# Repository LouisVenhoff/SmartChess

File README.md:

# SmartChessBoard

Repository for development of an Smart Chess Board (Hardware and Software)

Further coming soon...

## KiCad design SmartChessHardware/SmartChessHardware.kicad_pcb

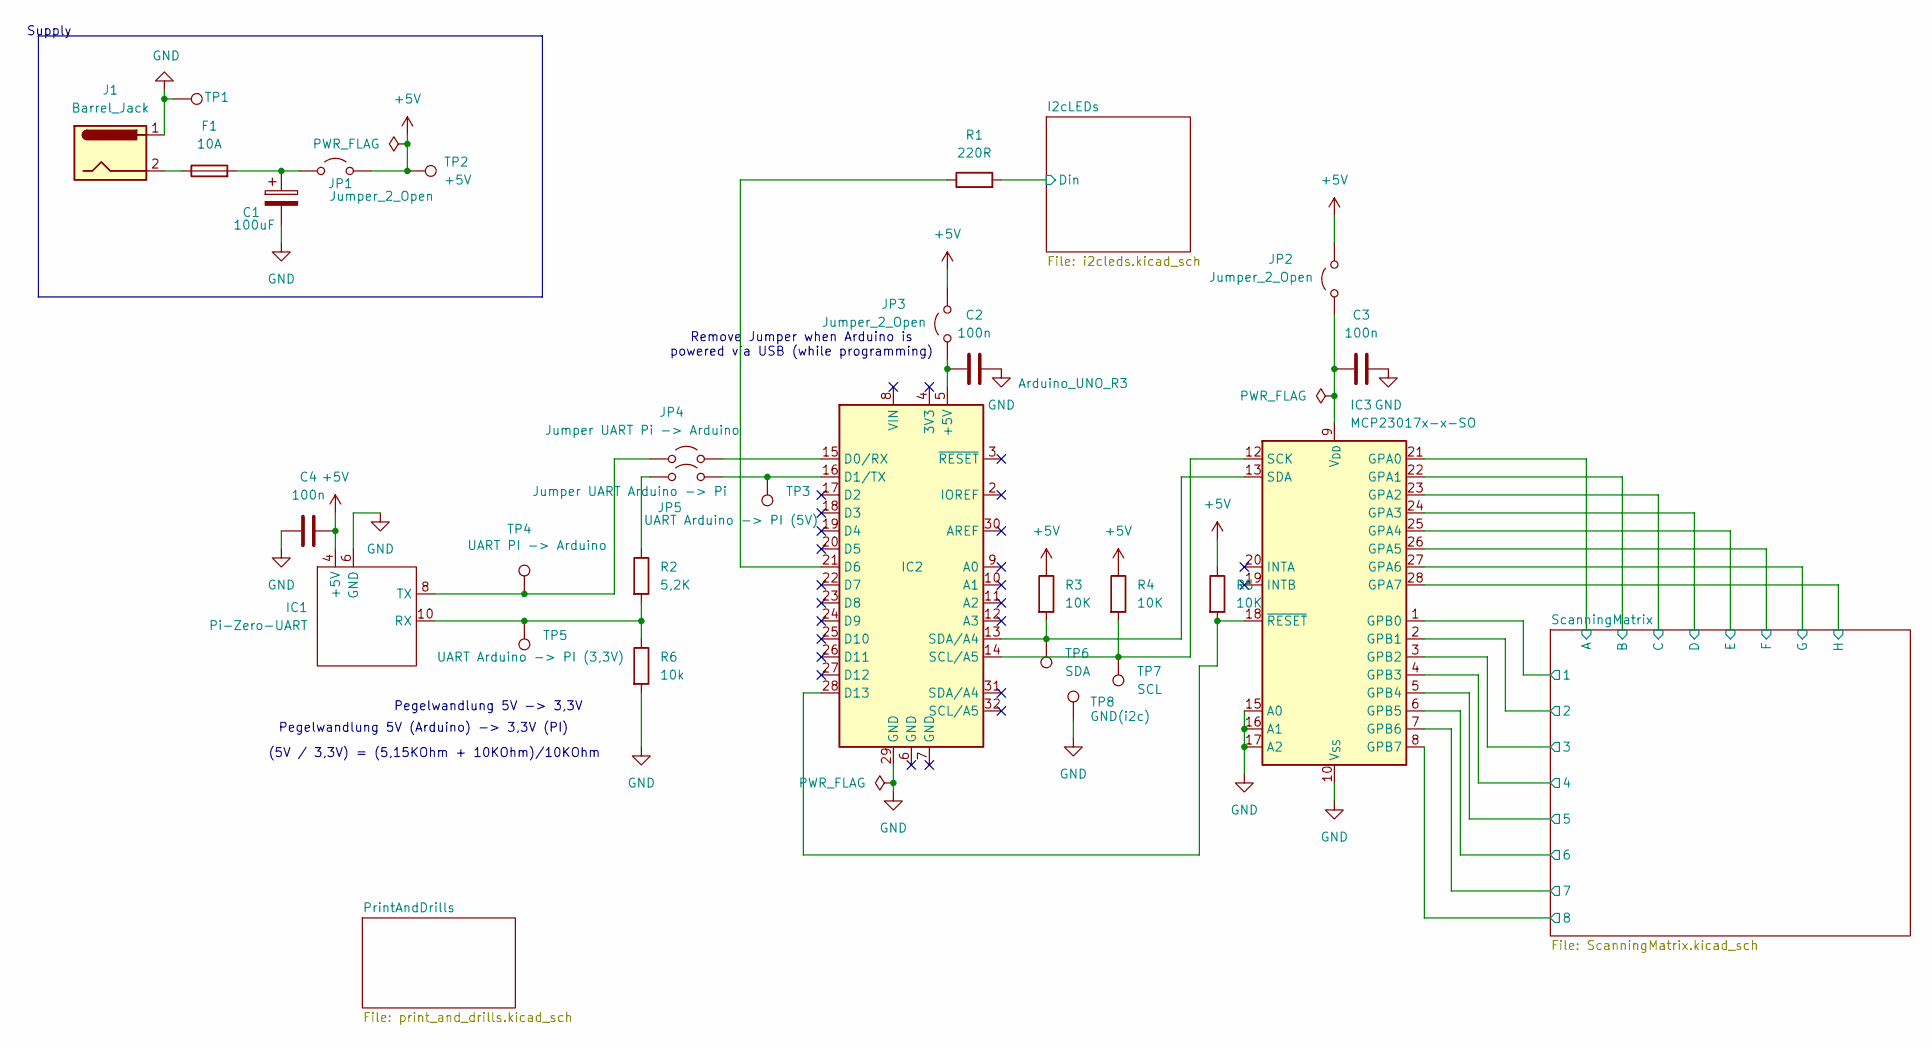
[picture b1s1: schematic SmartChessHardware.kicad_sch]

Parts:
C1: 100uF; CP_Radial_D6.3mm_P2.50mm
C2, C3, C4: 100n; C_0603_1608Metric
F1: 10A; Fuse_0603_1608Metric
IC1: Pi-Zero-UART; Raspberry_Pi_Zero_Socketed_THT_FaceDown_MountingHoles
IC2: Arduino_UNO_R3
IC3: MCP23017x-x-SO; SOIC-28W_7.5x17.9mm_P1.27mm
J1: Barrel_Jack; BarrelJack_GCT_DCJ200-10-A_Horizontal
JP1, JP2, JP3: Jumper_2_Open; PinHeader_1x02_P1.00mm_Vertical
JP4: Jumper UART Pi -> Arduino; PinHeader_1x02_P1.00mm_Vertical
JP5: Jumper UART Arduino -> Pi; PinHeader_1x02_P1.00mm_Vertical
R1: 220R; R_0603_1608Metric
R2: 5,2K; R_0603_1608Metric
R3, R4, R5: 10K; R_0603_1608Metric
R6: 10k; R_0603_1608Metric
TP1: GND; TestPoint_THTPad_D2.0mm_Drill1.0mm
TP2: +5V; TestPoint_THTPad_D2.0mm_Drill1.0mm
TP3: UART Arduino -> PI (5V); TestPoint_THTPad_D2.0mm_Drill1.0mm
TP4: UART PI -> Arduino; TestPoint_THTPad_D2.0mm_Drill1.0mm
TP5: UART Arduino -> PI (3,3V); TestPoint_THTPad_D2.0mm_Drill1.0mm
TP6: SDA; TestPoint_THTPad_D2.0mm_Drill1.0mm
TP7: SCL; TestPoint_THTPad_D2.0mm_Drill1.0mm
TP8: GND(i2c); TestPoint_THTPad_D2.0mm_Drill1.0mm

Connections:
+5V: C4.1, IC1.4 (+5V), JP1.2 (B), JP2.2 (B), JP3.2 (B), R3.1, R4.1, R5.1, TP2.1 (1_1); also elsewhere on the board
/I2cLEDs/Din: R1.2; also elsewhere on the board
/ScanningMatrix/1: IC3.1 (GPB0); also elsewhere on the board
/ScanningMatrix/2: IC3.2 (GPB1); also elsewhere on the board
/ScanningMatrix/3: IC3.3 (GPB2); also elsewhere on the board
/ScanningMatrix/4: IC3.4 (GPB3); also elsewhere on the board
/ScanningMatrix/5: IC3.5 (GPB4); also elsewhere on the board
/ScanningMatrix/6: IC3.6 (GPB5); also elsewhere on the board
/ScanningMatrix/7: IC3.7 (GPB6); also elsewhere on the board
/ScanningMatrix/8: IC3.8 (GPB7); also elsewhere on the board
/ScanningMatrix/A: IC3.21 (GPA0); also elsewhere on the board
/ScanningMatrix/B: IC3.22 (GPA1); also elsewhere on the board
/ScanningMatrix/C: IC3.23 (GPA2); also elsewhere on the board
/ScanningMatrix/D: IC3.24 (GPA3); also elsewhere on the board
/ScanningMatrix/E: IC3.25 (GPA4); also elsewhere on the board
/ScanningMatrix/F: IC3.26 (GPA5); also elsewhere on the board
/ScanningMatrix/G: IC3.27 (GPA6); also elsewhere on the board
/ScanningMatrix/H: IC3.28 (GPA7); also elsewhere on the board
GND: C1.2, C2.2, C3.2, C4.2, IC1.6 (GND), IC2.29 (GND), IC3.10 (V_{SS}), IC3.15 (A0), IC3.16 (A1), IC3.17 (A2), J1.1, R6.2, TP1.1 (1_1), TP8.1 (1_1); also elsewhere on the board
unnamed: F1.1, J1.2
unnamed: IC1.10 (RX), R2.2, R6.1, TP5.1 (1_1)
unnamed: IC1.8 (TX), JP4.1 (A), TP4.1 (1_1)
unnamed: C2.1, IC2.5 (+5V), JP3.1 (A)
unnamed: IC2.15 (D0/RX), JP4.2 (B)
unnamed: IC2.16 (D1/TX), JP5.2 (B), TP3.1 (1_1)
unnamed: IC2.21 (D6), R1.1
unnamed: IC2.28 (D13), IC3.18 (~RESET), R5.2
unnamed: IC2.14 (SCL/A5), IC3.12 (SCK), R4.2, TP7.1 (1_1)
unnamed: IC2.13 (SDA/A4), IC3.13 (SDA), R3.2, TP6.1 (1_1)
unnamed: C3.1, IC3.9 (V_{DD}), JP2.1 (A)
unnamed: C1.1, F1.2, JP1.1 (A)
unnamed: JP5.1 (A), R2.1

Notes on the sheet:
(5V / 3,3V) = (5,15KOhm + 10KOhm)/10KOhm
Remove Jumper when Arduino is powered via USB (while programming)
Pegelwandlung 5V -> 3,3V
Pegelwandlung 5V (Arduino) -> 3,3V (PI)
Supply

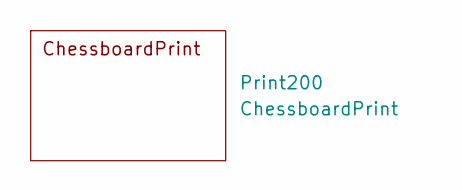
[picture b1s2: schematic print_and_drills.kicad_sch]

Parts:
Print200: ChessboardPrint; ChessBoard

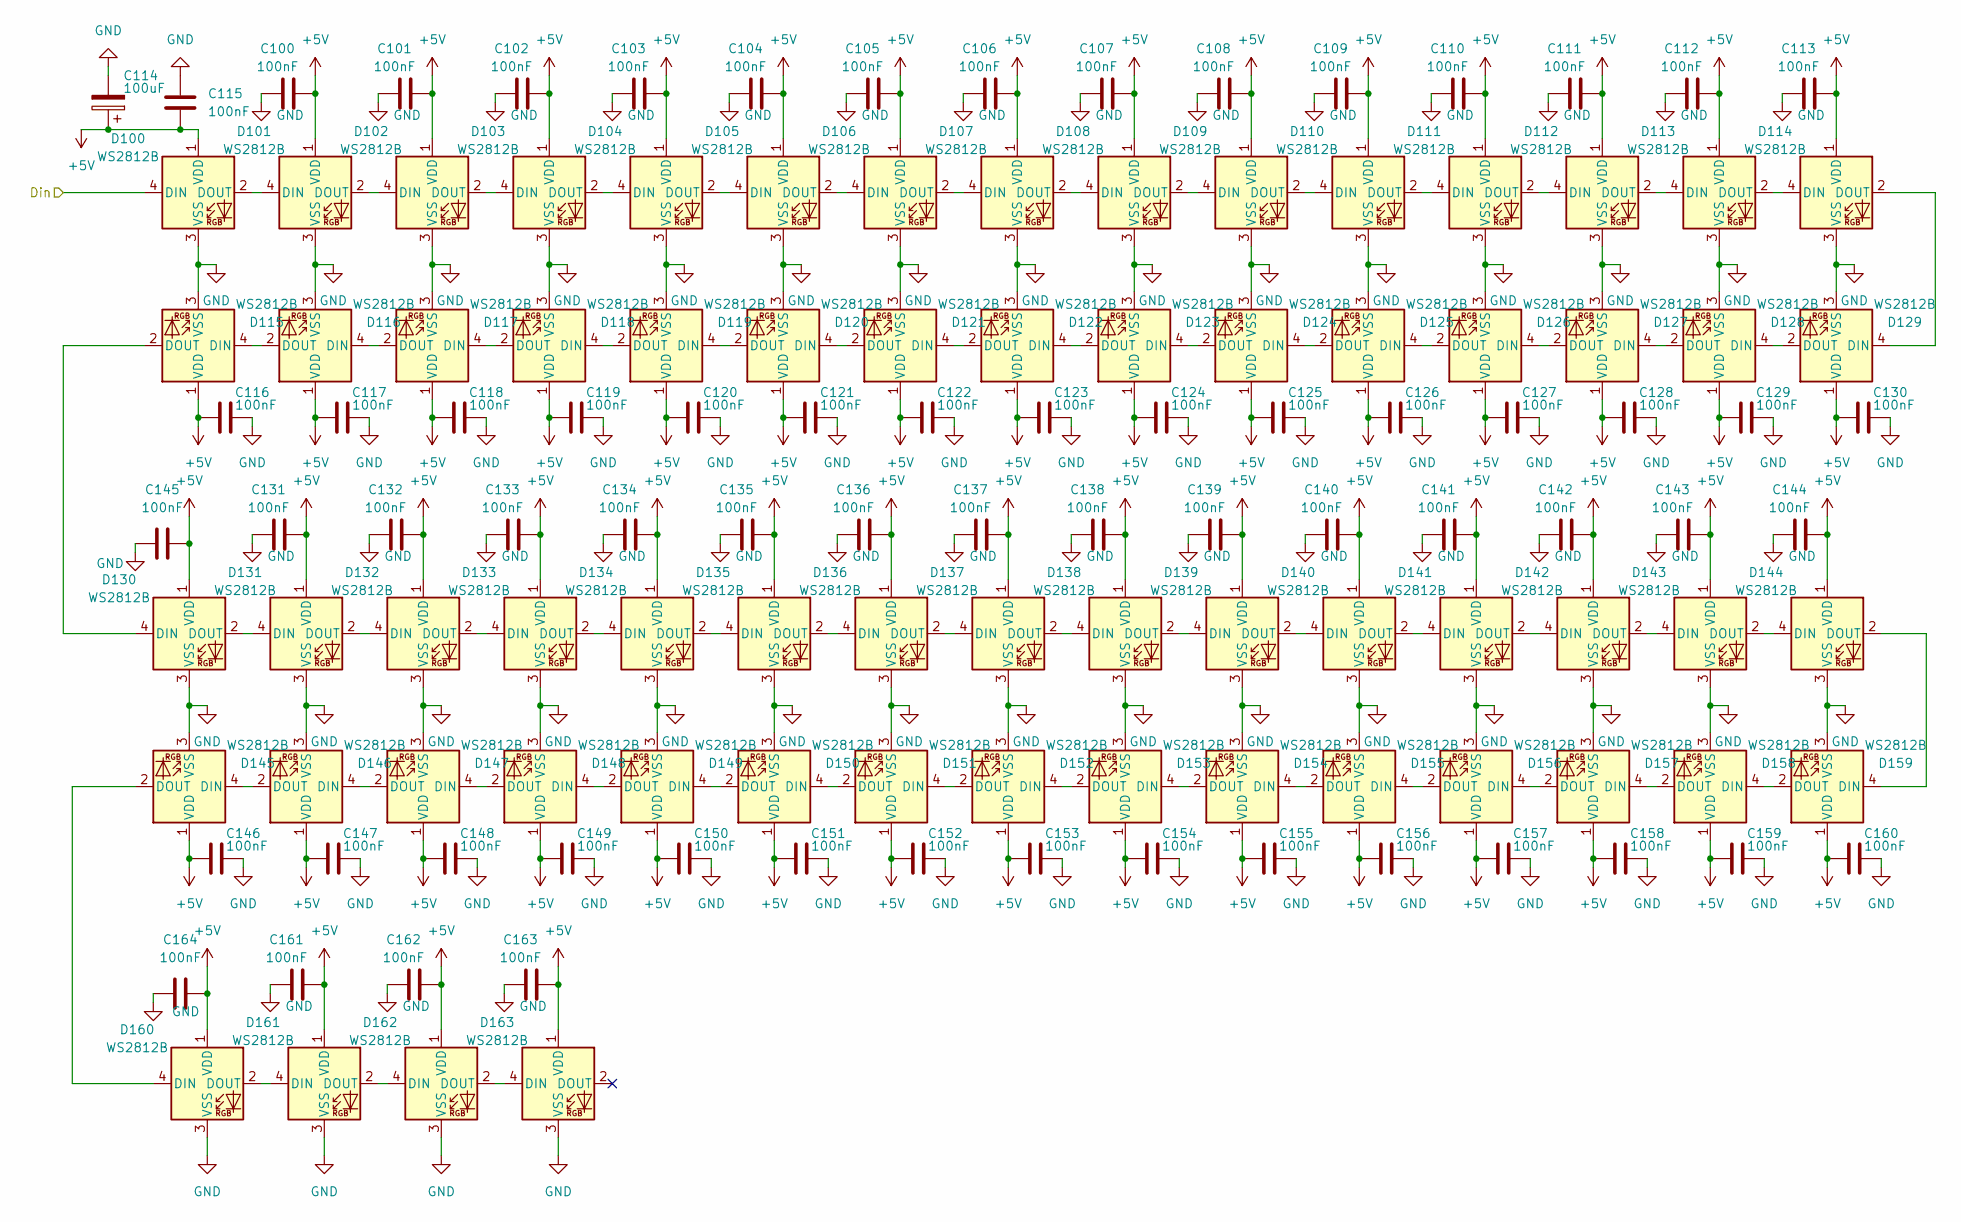
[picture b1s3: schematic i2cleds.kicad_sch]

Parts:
C100, C101, C102, C103, C104, C105, C106, C107, C108, C109, C110, C111, C112, C113, C115, C116, C117, C118, C119, C120, C121, C122, C123, C124, C125, C126, C127, C128, C129, C130, C131, C132, C133, C134, C135, C136, C137, C138, C139, C140, C141, C142, C143, C144, C145, C146, C147, C148, C149, C150, C151, C152, C153, C154, C155, C156, C157, C158, C159, C160, C161, C162, C163, C164: 100nF; C_0603_1608Metric
C114: 100uF; CP_Radial_D6.3mm_P2.50mm
D100, D101, D102, D103, D104, D105, D106, D107, D108, D109, D110, D111, D112, D113, D114, D115, D116, D117, D118, D119, D120, D121, D122, D123, D124, D125, D126, D127, D128, D129, D130, D131, D132, D133, D134, D135, D136, D137, D138, D139, D140, D141, D142, D143, D144, D145, D146, D147, D148, D149, D150, D151, D152, D153, D154, D155, D156, D157, D158, D159, D160, D161, D162, D163: WS2812B; LED_WS2812B_PLCC4_5.0x5.0mm_P3.2mm

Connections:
+5V: C100.2, C101.2, C102.2, C103.2, C104.2, C105.2, C106.2, C107.2, C108.2, C109.2, C110.2, C111.2, C112.2, C113.2, C114.1, C115.2, C116.1, C117.1, C118.1, C119.1, C120.1, C121.1, C122.1, C123.1, C124.1, C125.1, C126.1, C127.1, C128.1, C129.1, C130.1, C131.2, C132.2, C133.2, C134.2, C135.2, C136.2, C137.2, C138.2, C139.2, C140.2, C141.2, C142.2, C143.2, C144.2, C145.2, C146.1, C147.1, C148.1, C149.1, C150.1, C151.1, C152.1, C153.1, C154.1, C155.1, C156.1, C157.1, C158.1, C159.1, C160.1, C161.2, C162.2, C163.2, C164.2, D100.1 (VDD), D101.1 (VDD), D102.1 (VDD), D103.1 (VDD), D104.1 (VDD), D105.1 (VDD), D106.1 (VDD), D107.1 (VDD), D108.1 (VDD), D109.1 (VDD), D110.1 (VDD), D111.1 (VDD), D112.1 (VDD), D113.1 (VDD), D114.1 (VDD), D115.1 (VDD), D116.1 (VDD), D117.1 (VDD), D118.1 (VDD), D119.1 (VDD), D120.1 (VDD), D121.1 (VDD), D122.1 (VDD), D123.1 (VDD), D124.1 (VDD), D125.1 (VDD), D126.1 (VDD), D127.1 (VDD), D128.1 (VDD), D129.1 (VDD), D130.1 (VDD), D131.1 (VDD), D132.1 (VDD), D133.1 (VDD), D134.1 (VDD), D135.1 (VDD), D136.1 (VDD), D137.1 (VDD), D138.1 (VDD), D139.1 (VDD), D140.1 (VDD), D141.1 (VDD), D142.1 (VDD), D143.1 (VDD), D144.1 (VDD), D145.1 (VDD), D146.1 (VDD), D147.1 (VDD), D148.1 (VDD), D149.1 (VDD), D150.1 (VDD), D151.1 (VDD), D152.1 (VDD), D153.1 (VDD), D154.1 (VDD), D155.1 (VDD), D156.1 (VDD), D157.1 (VDD), D158.1 (VDD), D159.1 (VDD), D160.1 (VDD), D161.1 (VDD), D162.1 (VDD), D163.1 (VDD); also elsewhere on the board
/I2cLEDs/Din: D100.4 (DIN); also elsewhere on the board
GND: C100.1, C101.1, C102.1, C103.1, C104.1, C105.1, C106.1, C107.1, C108.1, C109.1, C110.1, C111.1, C112.1, C113.1, C114.2, C115.1, C116.2, C117.2, C118.2, C119.2, C120.2, C121.2, C122.2, C123.2, C124.2, C125.2, C126.2, C127.2, C128.2, C129.2, C130.2, C131.1, C132.1, C133.1, C134.1, C135.1, C136.1, C137.1, C138.1, C139.1, C140.1, C141.1, C142.1, C143.1, C144.1, C145.1, C146.2, C147.2, C148.2, C149.2, C150.2, C151.2, C152.2, C153.2, C154.2, C155.2, C156.2, C157.2, C158.2, C159.2, C160.2, C161.1, C162.1, C163.1, C164.1, D100.3 (VSS), D101.3 (VSS), D102.3 (VSS), D103.3 (VSS), D104.3 (VSS), D105.3 (VSS), D106.3 (VSS), D107.3 (VSS), D108.3 (VSS), D109.3 (VSS), D110.3 (VSS), D111.3 (VSS), D112.3 (VSS), D113.3 (VSS), D114.3 (VSS), D115.3 (VSS), D116.3 (VSS), D117.3 (VSS), D118.3 (VSS), D119.3 (VSS), D120.3 (VSS), D121.3 (VSS), D122.3 (VSS), D123.3 (VSS), D124.3 (VSS), D125.3 (VSS), D126.3 (VSS), D127.3 (VSS), D128.3 (VSS), D129.3 (VSS), D130.3 (VSS), D131.3 (VSS), D132.3 (VSS), D133.3 (VSS), D134.3 (VSS), D135.3 (VSS), D136.3 (VSS), D137.3 (VSS), D138.3 (VSS), D139.3 (VSS), D140.3 (VSS), D141.3 (VSS), D142.3 (VSS), D143.3 (VSS), D144.3 (VSS), D145.3 (VSS), D146.3 (VSS), D147.3 (VSS), D148.3 (VSS), D149.3 (VSS), D150.3 (VSS), D151.3 (VSS), D152.3 (VSS), D153.3 (VSS), D154.3 (VSS), D155.3 (VSS), D156.3 (VSS), D157.3 (VSS), D158.3 (VSS), D159.3 (VSS), D160.3 (VSS), D161.3 (VSS), D162.3 (VSS), D163.3 (VSS); also elsewhere on the board
unnamed: D100.2 (DOUT), D101.4 (DIN)
unnamed: D101.2 (DOUT), D102.4 (DIN)
unnamed: D102.2 (DOUT), D103.4 (DIN)
unnamed: D103.2 (DOUT), D104.4 (DIN)
unnamed: D104.2 (DOUT), D105.4 (DIN)
unnamed: D105.2 (DOUT), D106.4 (DIN)
unnamed: D106.2 (DOUT), D107.4 (DIN)
unnamed: D107.2 (DOUT), D108.4 (DIN)
unnamed: D108.2 (DOUT), D109.4 (DIN)
unnamed: D109.2 (DOUT), D110.4 (DIN)
unnamed: D110.2 (DOUT), D111.4 (DIN)
unnamed: D111.2 (DOUT), D112.4 (DIN)
unnamed: D112.2 (DOUT), D113.4 (DIN)
unnamed: D113.2 (DOUT), D114.4 (DIN)
unnamed: D114.2 (DOUT), D129.4 (DIN)
unnamed: D115.4 (DIN), D116.2 (DOUT)
unnamed: D115.2 (DOUT), D130.4 (DIN)
unnamed: D116.4 (DIN), D117.2 (DOUT)
unnamed: D117.4 (DIN), D118.2 (DOUT)
unnamed: D118.4 (DIN), D119.2 (DOUT)
unnamed: D119.4 (DIN), D120.2 (DOUT)
unnamed: D120.4 (DIN), D121.2 (DOUT)
unnamed: D121.4 (DIN), D122.2 (DOUT)
unnamed: D122.4 (DIN), D123.2 (DOUT)
unnamed: D123.4 (DIN), D124.2 (DOUT)
unnamed: D124.4 (DIN), D125.2 (DOUT)
unnamed: D125.4 (DIN), D126.2 (DOUT)
unnamed: D126.4 (DIN), D127.2 (DOUT)
unnamed: D127.4 (DIN), D128.2 (DOUT)
unnamed: D128.4 (DIN), D129.2 (DOUT)
unnamed: D130.2 (DOUT), D131.4 (DIN)
unnamed: D131.2 (DOUT), D132.4 (DIN)
unnamed: D132.2 (DOUT), D133.4 (DIN)
unnamed: D133.2 (DOUT), D134.4 (DIN)
unnamed: D134.2 (DOUT), D135.4 (DIN)
unnamed: D135.2 (DOUT), D136.4 (DIN)
unnamed: D136.2 (DOUT), D137.4 (DIN)
unnamed: D137.2 (DOUT), D138.4 (DIN)
unnamed: D138.2 (DOUT), D139.4 (DIN)
unnamed: D139.2 (DOUT), D140.4 (DIN)
unnamed: D140.2 (DOUT), D141.4 (DIN)
unnamed: D141.2 (DOUT), D142.4 (DIN)
unnamed: D142.2 (DOUT), D143.4 (DIN)
unnamed: D143.2 (DOUT), D144.4 (DIN)
unnamed: D144.2 (DOUT), D159.4 (DIN)
unnamed: D145.4 (DIN), D146.2 (DOUT)
unnamed: D145.2 (DOUT), D160.4 (DIN)
unnamed: D146.4 (DIN), D147.2 (DOUT)
unnamed: D147.4 (DIN), D148.2 (DOUT)
unnamed: D148.4 (DIN), D149.2 (DOUT)
unnamed: D149.4 (DIN), D150.2 (DOUT)
unnamed: D150.4 (DIN), D151.2 (DOUT)
unnamed: D151.4 (DIN), D152.2 (DOUT)
unnamed: D152.4 (DIN), D153.2 (DOUT)
unnamed: D153.4 (DIN), D154.2 (DOUT)
unnamed: D154.4 (DIN), D155.2 (DOUT)
unnamed: D155.4 (DIN), D156.2 (DOUT)
unnamed: D156.4 (DIN), D157.2 (DOUT)
unnamed: D157.4 (DIN), D158.2 (DOUT)
unnamed: D158.4 (DIN), D159.2 (DOUT)
unnamed: D160.2 (DOUT), D161.4 (DIN)
unnamed: D161.2 (DOUT), D162.4 (DIN)
unnamed: D162.2 (DOUT), D163.4 (DIN)

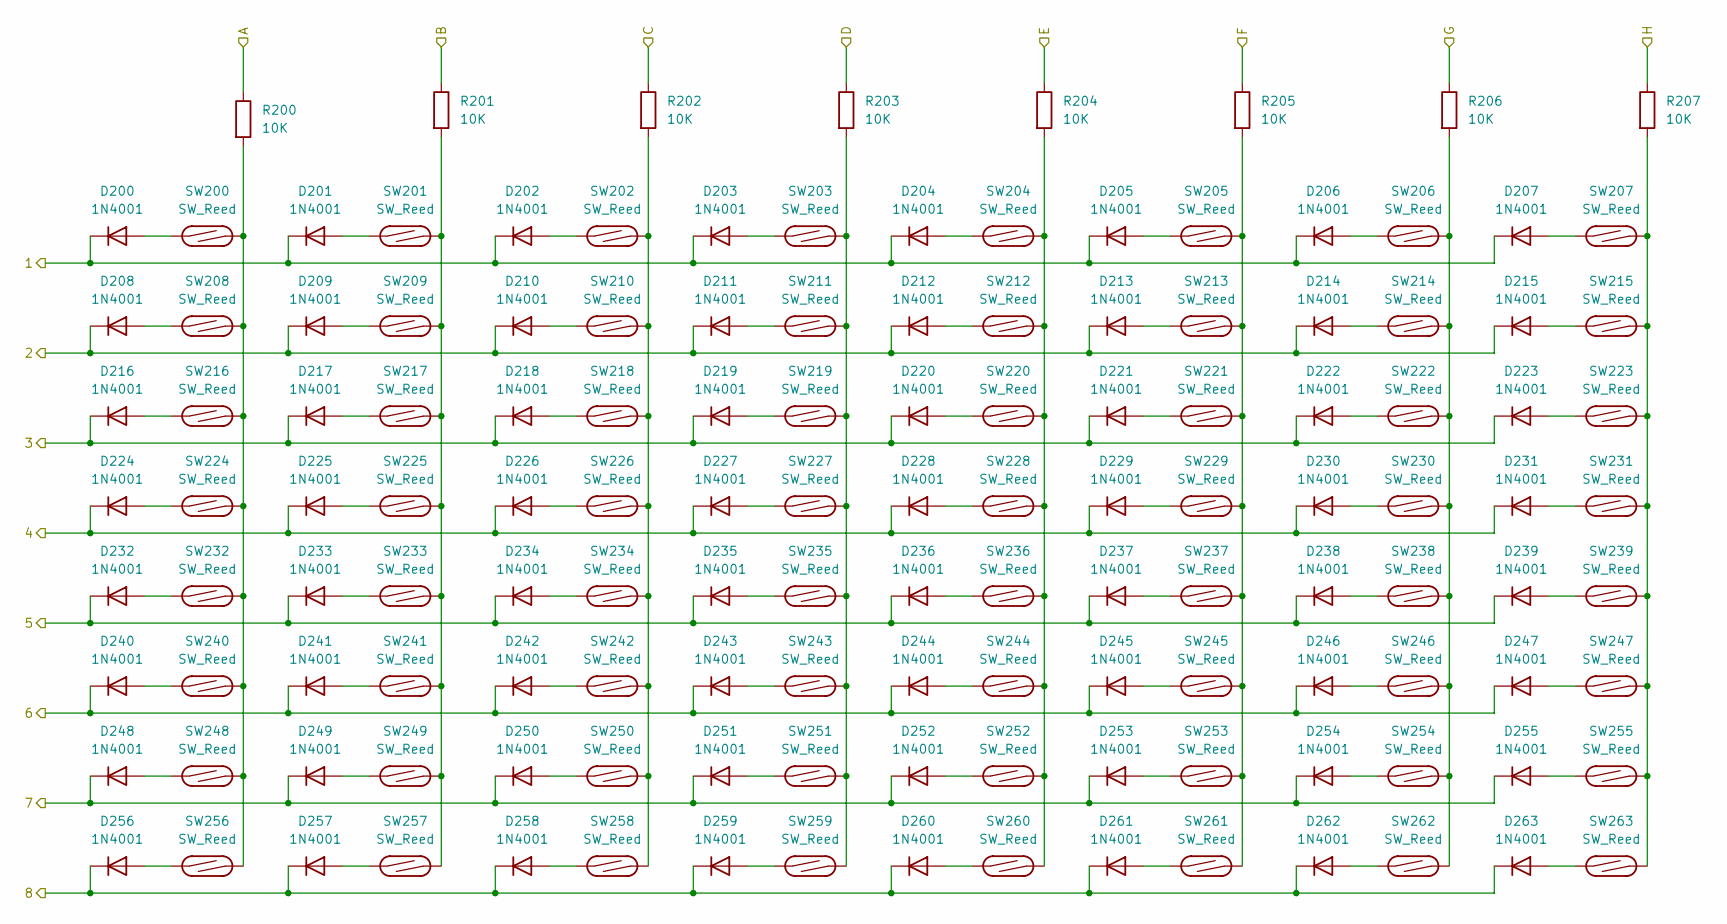
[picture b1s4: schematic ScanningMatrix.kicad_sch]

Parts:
D200, D201, D202, D203, D204, D205, D206, D207, D208, D209, D210, D211, D212, D213, D214, D215, D216, D217, D218, D219, D220, D221, D222, D223, D224, D225, D226, D227, D228, D229, D230, D231, D232, D233, D234, D235, D236, D237, D238, D239, D240, D241, D242, D243, D244, D245, D246, D247, D248, D249, D250, D251, D252, D253, D254, D255, D256, D257, D258, D259, D260, D261, D262, D263: 1N4001; D_SMA
R200, R201, R202, R203, R204, R205, R206, R207: 10K; R_0603_1608Metric
SW200, SW201, SW202, SW203, SW204, SW205, SW206, SW207, SW208, SW209, SW210, SW211, SW212, SW213, SW214, SW215, SW216, SW217, SW218, SW219, SW220, SW221, SW222, SW223, SW224, SW225, SW226, SW227, SW228, SW229, SW230, SW231, SW232, SW233, SW234, SW235, SW236, SW237, SW238, SW239, SW240, SW241, SW242, SW243, SW244, SW245, SW246, SW247, SW248, SW249, SW250, SW251, SW252, SW253, SW254, SW255, SW256, SW257, SW258, SW259, SW260, SW261, SW262, SW263: SW_Reed; R_Axial_DIN0309_L9.0mm_D3.2mm_P20.32mm_Horizontal

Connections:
/ScanningMatrix/1: D200.1 (K), D201.1 (K), D202.1 (K), D203.1 (K), D204.1 (K), D205.1 (K), D206.1 (K), D207.1 (K); also elsewhere on the board
/ScanningMatrix/2: D208.1 (K), D209.1 (K), D210.1 (K), D211.1 (K), D212.1 (K), D213.1 (K), D214.1 (K), D215.1 (K); also elsewhere on the board
/ScanningMatrix/3: D216.1 (K), D217.1 (K), D218.1 (K), D219.1 (K), D220.1 (K), D221.1 (K), D222.1 (K), D223.1 (K); also elsewhere on the board
/ScanningMatrix/4: D224.1 (K), D225.1 (K), D226.1 (K), D227.1 (K), D228.1 (K), D229.1 (K), D230.1 (K), D231.1 (K); also elsewhere on the board
/ScanningMatrix/5: D232.1 (K), D233.1 (K), D234.1 (K), D235.1 (K), D236.1 (K), D237.1 (K), D238.1 (K), D239.1 (K); also elsewhere on the board
/ScanningMatrix/6: D240.1 (K), D241.1 (K), D242.1 (K), D243.1 (K), D244.1 (K), D245.1 (K), D246.1 (K), D247.1 (K); also elsewhere on the board
/ScanningMatrix/7: D248.1 (K), D249.1 (K), D250.1 (K), D251.1 (K), D252.1 (K), D253.1 (K), D254.1 (K), D255.1 (K); also elsewhere on the board
/ScanningMatrix/8: D256.1 (K), D257.1 (K), D258.1 (K), D259.1 (K), D260.1 (K), D261.1 (K), D262.1 (K), D263.1 (K); also elsewhere on the board
/ScanningMatrix/A: R200.1; also elsewhere on the board
/ScanningMatrix/B: R201.1; also elsewhere on the board
/ScanningMatrix/C: R202.1; also elsewhere on the board
/ScanningMatrix/D: R203.1; also elsewhere on the board
/ScanningMatrix/E: R204.1; also elsewhere on the board
/ScanningMatrix/F: R205.1; also elsewhere on the board
/ScanningMatrix/G: R206.1; also elsewhere on the board
/ScanningMatrix/H: R207.1; also elsewhere on the board
unnamed: D200.2 (A), SW200.1
unnamed: D201.2 (A), SW201.1
unnamed: D202.2 (A), SW202.1
unnamed: D203.2 (A), SW203.1
unnamed: D204.2 (A), SW204.1
unnamed: D205.2 (A), SW205.1
unnamed: D206.2 (A), SW206.1
unnamed: D207.2 (A), SW207.1
unnamed: D208.2 (A), SW208.1
unnamed: D209.2 (A), SW209.1
unnamed: D210.2 (A), SW210.1
unnamed: D211.2 (A), SW211.1
unnamed: D212.2 (A), SW212.1
unnamed: D213.2 (A), SW213.1
unnamed: D214.2 (A), SW214.1
unnamed: D215.2 (A), SW215.1
unnamed: D216.2 (A), SW216.1
unnamed: D217.2 (A), SW217.1
unnamed: D218.2 (A), SW218.1
unnamed: D219.2 (A), SW219.1
unnamed: D220.2 (A), SW220.1
unnamed: D221.2 (A), SW221.1
unnamed: D222.2 (A), SW222.1
unnamed: D223.2 (A), SW223.1
unnamed: D224.2 (A), SW224.1
unnamed: D225.2 (A), SW225.1
unnamed: D226.2 (A), SW226.1
unnamed: D227.2 (A), SW227.1
unnamed: D228.2 (A), SW228.1
unnamed: D229.2 (A), SW229.1
unnamed: D230.2 (A), SW230.1
unnamed: D231.2 (A), SW231.1
unnamed: D232.2 (A), SW232.1
unnamed: D233.2 (A), SW233.1
unnamed: D234.2 (A), SW234.1
unnamed: D235.2 (A), SW235.1
unnamed: D236.2 (A), SW236.1
unnamed: D237.2 (A), SW237.1
unnamed: D238.2 (A), SW238.1
unnamed: D239.2 (A), SW239.1
unnamed: D240.2 (A), SW240.1
unnamed: D241.2 (A), SW241.1
unnamed: D242.2 (A), SW242.1
unnamed: D243.2 (A), SW243.1
unnamed: D244.2 (A), SW244.1
unnamed: D245.2 (A), SW245.1
unnamed: D246.2 (A), SW246.1
unnamed: D247.2 (A), SW247.1
unnamed: D248.2 (A), SW248.1
unnamed: D249.2 (A), SW249.1
unnamed: D250.2 (A), SW250.1
unnamed: D251.2 (A), SW251.1
unnamed: D252.2 (A), SW252.1
unnamed: D253.2 (A), SW253.1
unnamed: D254.2 (A), SW254.1
unnamed: D255.2 (A), SW255.1
unnamed: D256.2 (A), SW256.1
unnamed: D257.2 (A), SW257.1
unnamed: D258.2 (A), SW258.1
unnamed: D259.2 (A), SW259.1
unnamed: D260.2 (A), SW260.1
unnamed: D261.2 (A), SW261.1
unnamed: D262.2 (A), SW262.1
unnamed: D263.2 (A), SW263.1
unnamed: R200.2, SW200.2, SW208.2, SW216.2, SW224.2, SW232.2, SW240.2, SW248.2, SW256.2
unnamed: R201.2, SW201.2, SW209.2, SW217.2, SW225.2, SW233.2, SW241.2, SW249.2, SW257.2
unnamed: R202.2, SW202.2, SW210.2, SW218.2, SW226.2, SW234.2, SW242.2, SW250.2, SW258.2
unnamed: R203.2, SW203.2, SW211.2, SW219.2, SW227.2, SW235.2, SW243.2, SW251.2, SW259.2
unnamed: R204.2, SW204.2, SW212.2, SW220.2, SW228.2, SW236.2, SW244.2, SW252.2, SW260.2
unnamed: R205.2, SW205.2, SW213.2, SW221.2, SW229.2, SW237.2, SW245.2, SW253.2, SW261.2
unnamed: R206.2, SW206.2, SW214.2, SW222.2, SW230.2, SW238.2, SW246.2, SW254.2, SW262.2
unnamed: R207.2, SW207.2, SW215.2, SW223.2, SW231.2, SW239.2, SW247.2, SW255.2, SW263.2

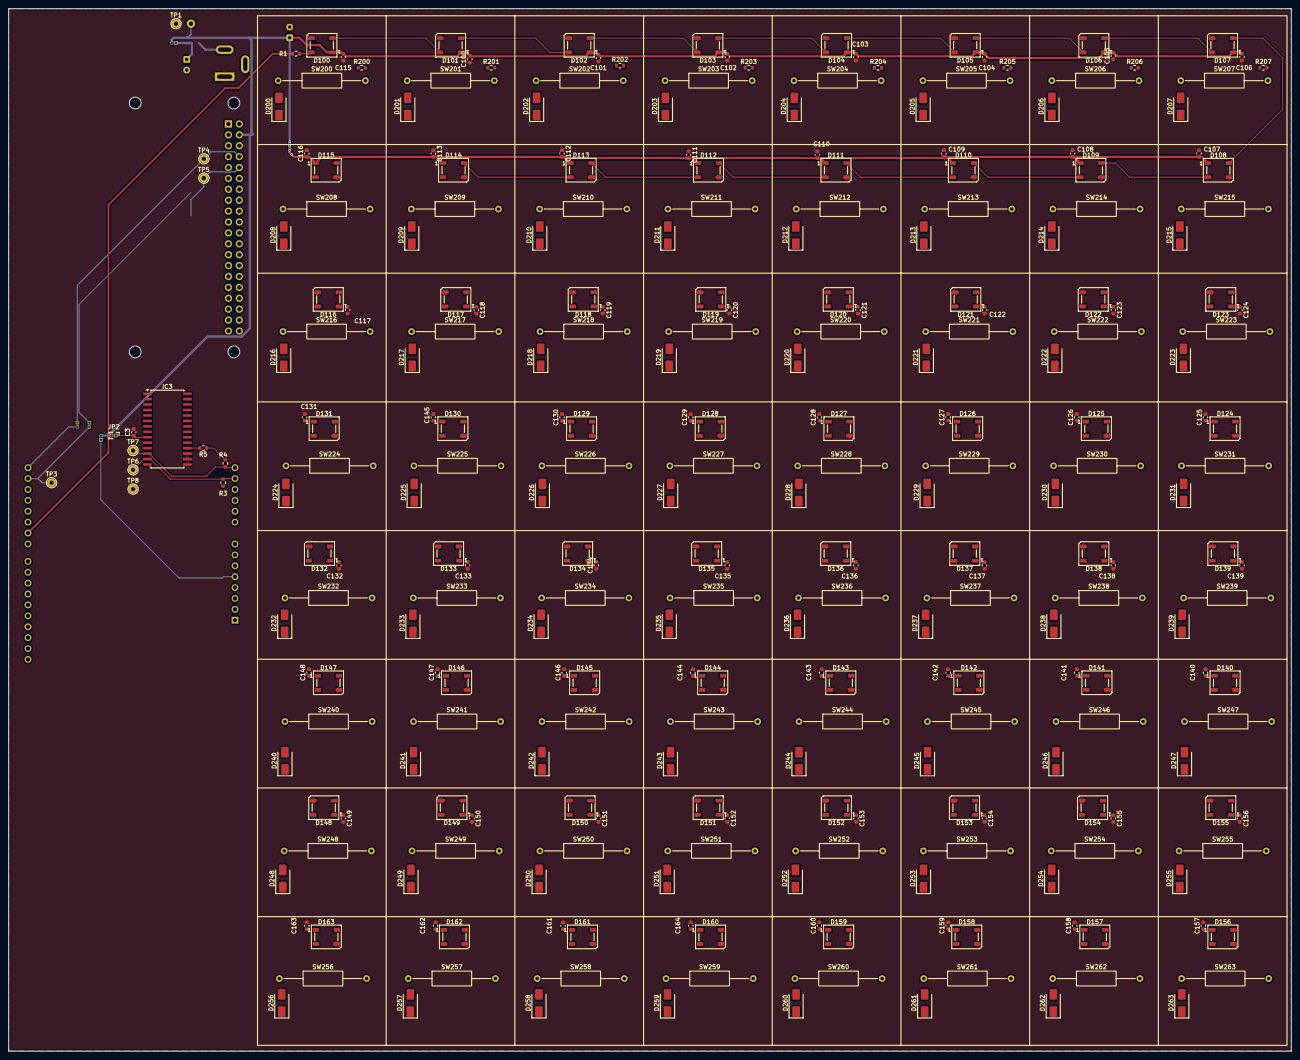
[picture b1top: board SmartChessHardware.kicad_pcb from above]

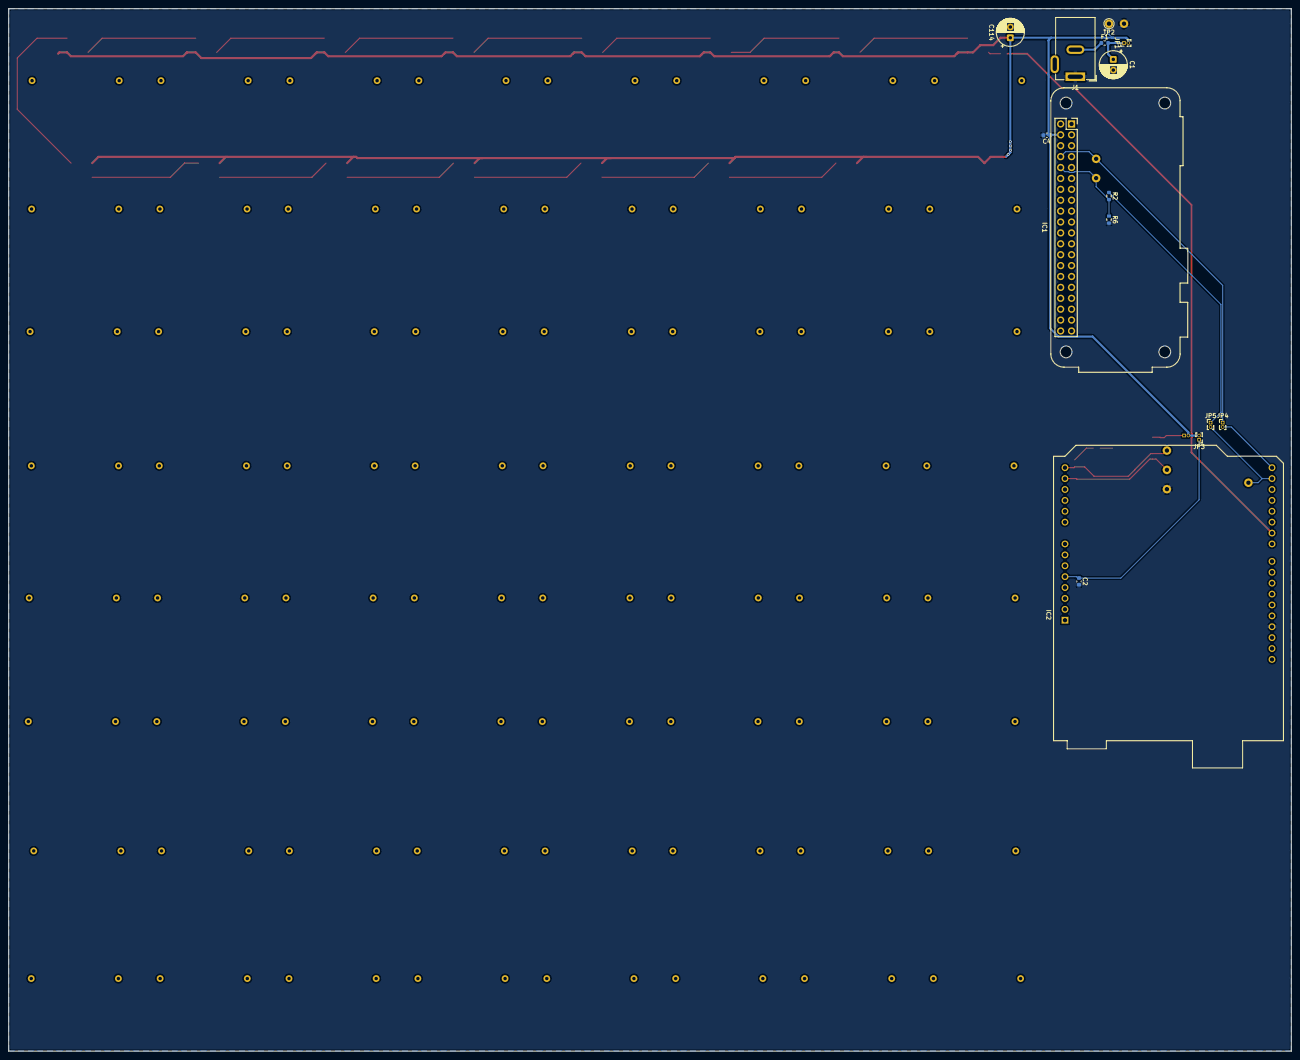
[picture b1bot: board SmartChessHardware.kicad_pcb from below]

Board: 2 copper layers, 299.0 x 243.0 mm, 294 parts (15 on the bottom side), 167 nets.

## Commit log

2026-05-16 Add README for SmartChessBoard project
    Initial README file for SmartChessBoard project.
2026-05-16 Added jumper to disconnect UART
2026-05-16 Added custom footprint
2026-05-16 Added Chessboard Symbol
2026-05-24 Assigned Footprints
2026-05-25 Reworked supply circuit
2026-05-25 Added sheept for print
2026-05-25 Worked on PCB
2026-05-31 Placed board components
2026-05-31 Created Group for each reed diode group
2026-05-31 Rearranged scanning groups
2026-05-31 Fixed led placing
2026-05-31 Aligned LEDS
2026-05-31 Aligned no key ghosting diodes
2026-05-31 Placed Matrix pull up resistors
2026-05-31 Fixed wrong placed diodes
2026-05-31 Placed filtering capacitors for leds
2026-06-04 Layout wip
